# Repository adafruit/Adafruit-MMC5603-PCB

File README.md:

## Adafruit MMC5603 Triple-axis Magnetometer PCB

<a href="http://www.adafruit.com/products/5579"><br/>
Click here to purchase one from the Adafruit shop</a>

PCB files for the Adafruit MMC5603 Triple-axis Magnetometer. 

Format is EagleCAD schematic and board layout
* https://www.adafruit.com/product/5579

### Description

Sense the magnetic fields surrounding us with this handy triple-axis magnetometer (compass) module. Magnetometers can sense where the strongest magnetic force is coming from, generally used to detect magnetic north, but can also be used for measuring magnetic fields. This sensor tends to be paired with a 6-DoF (degree of freedom) accelerometer/gyroscope to create a 9-DoF inertial measurement unit that can detect its orientation in real-space thanks to Earth's stable magnetic field. It's a great match for the LSM6DSOX from ST!

We based this breakout on the MMC5603, a great general purpose magnetometer with a very wide range and bot I2C and SPI interfaces. This compact sensor uses I2C to communicate and it's very easy to use. Simply download our library and connect the SCL pin to your I2C clock pin, and SDA pin to your I2C data pin and upload our test program to read out magnetic field data. If you'd like, you can also use SPI to receive data (we just happen to prefer I2C here)

This sensor can sense ranges from ±30 Gauss (±3000uT or ±3mT) with no range-setting required and full 20 bit output up to 1000 Hz rate reading. The range makes it good for reading Earth's magnetic field (which maxes at about 0.6 Gauss) or some basic magnets. It isn't good for very strong rare earth magnets, for that check out the TLV293.

To make life easier so you can focus on your important work, we've taken the MMC5603 and put it onto a breakout PCB along with support circuitry to let you use this little wonder with 3.3V (Feather/Raspberry Pi) or 5V (Arduino/ Metro328) logic levels. Additionally, since it speaks I2C you can easily connect it up with two wires (plus power and ground!).  We've even included SparkFun qwiic compatible STEMMA QT connectors for the I2C bus so you don't even need to solder! Just wire up to your favorite micro and you can use our CircuitPython/Python or Arduino drivers to easily interface with the LIS2MDL and get magnetic measurements ASAP.

It's fully assembled and tested.  Comes with a bit of 0.1" standard header in case you want to use it with a breadboard or perfboard.  Four 2.5mm (0.1") mounting holes for easy attachment.

### License

Adafruit invests time and resources providing this open source design, please support Adafruit and open-source hardware by purchasing products from [Adafruit](https://www.adafruit.com)!

Designed by Limor Fried/Ladyada for Adafruit Industries.

Creative Commons Attribution/Share-Alike, all text above must be included in any redistribution. 
See license.txt for additional details.

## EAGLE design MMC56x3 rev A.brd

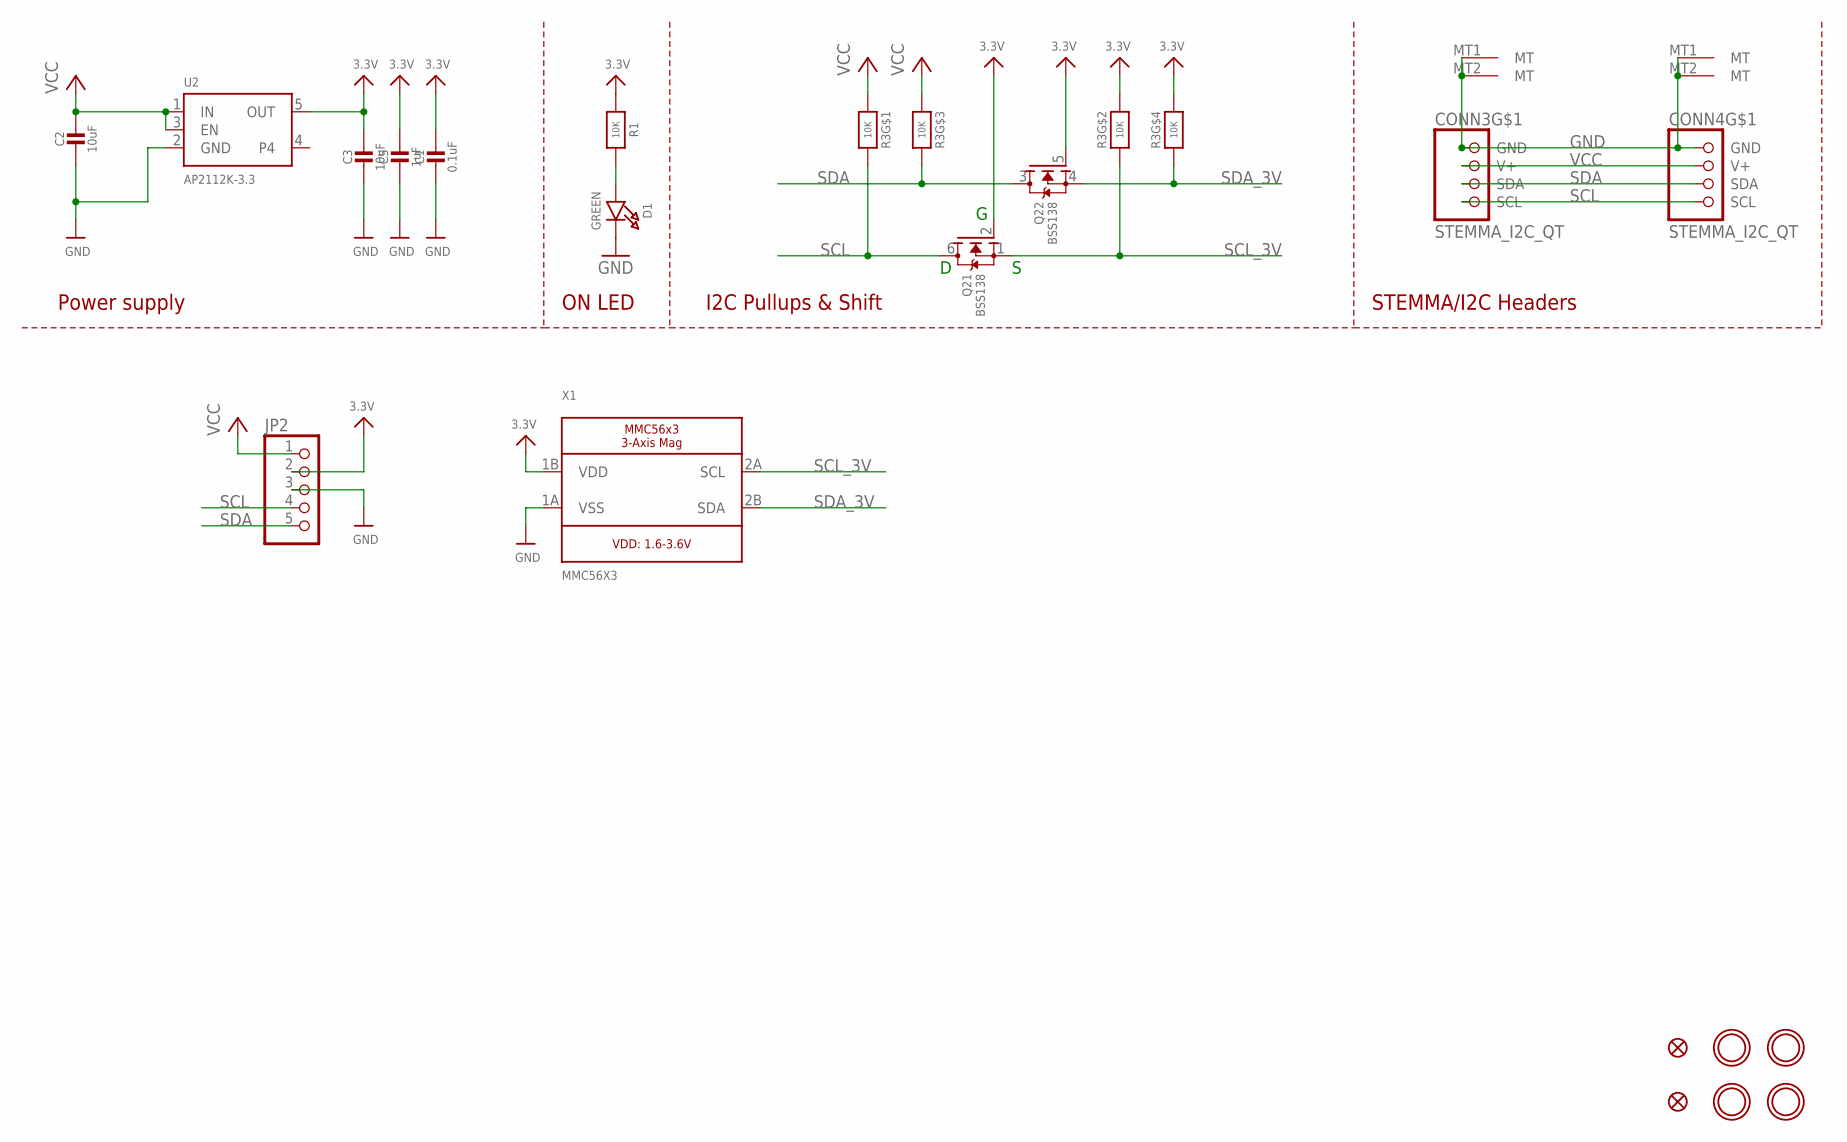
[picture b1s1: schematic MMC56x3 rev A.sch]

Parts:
C1: 0.1uF; 0603-NO
C2, C3: 10uF; 0805-NO
C5: 1uF; 0603-NO
CONN3, CONN4: STEMMA_I2C_QT; JST_SH4
D1: GREEN; CHIPLED_0603_NOOUTLINE
FID3, FID4: FIDUCIAL_1MM
JP2: HEADER-1X570MIL; 1X05_ROUND_70
Q2: BSS138; SOT363
R1: 10K; 0603-NO
R3: 10K; RESPACK_4X0603
U2: AP2112K-3.3; SOT23-5
U$1, U$2, U$4, U$17: MOUNTINGHOLE2.5; MOUNTINGHOLE_2.5_PLATED
X1: MMC56X3; WLP-4

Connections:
3.3V: C1.1, C3.1, C5.1, JP2.2, Q2.2 (G), Q2.5 (G), R1.1, R3.2 (1), R3.4 (1), U2.5 (OUT), X1.1B (VDD)
GND: C1.2, C2.2, C3.2, C5.2, CONN3.1 (GND), CONN3.MT1 (MT), CONN3.MT2 (MT), CONN4.1 (GND), CONN4.MT1 (MT), CONN4.MT2 (MT), D1.C, JP2.3, U2.2 (GND), X1.1A (VSS)
unnamed: D1.A, R1.2
SCL: CONN3.4 (SCL), CONN4.4 (SCL), JP2.4, Q2.6 (D), R3.8 (2)
SCL_3V: Q2.1 (S), R3.7 (2), X1.2A (SCL)
SDA: CONN3.3 (SDA), CONN4.3 (SDA), JP2.5, Q2.3 (D), R3.6 (2)
SDA_3V: Q2.4 (S), R3.5 (2), X1.2B (SDA)
VCC: C2.1, CONN3.2 (V+), CONN4.2 (V+), JP2.1, R3.1, R3.3 (1), U2.1 (IN), U2.3 (EN)

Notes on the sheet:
I2C Pullups & Shift
STEMMA/I2C Headers
ON LED
Power supply

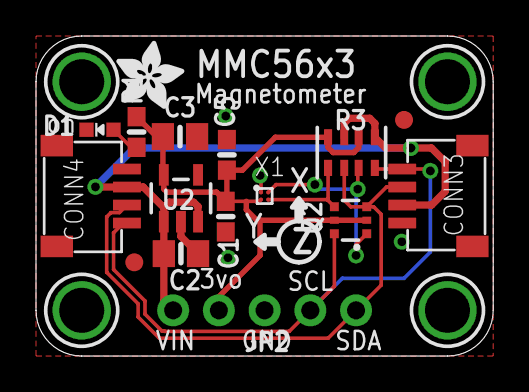
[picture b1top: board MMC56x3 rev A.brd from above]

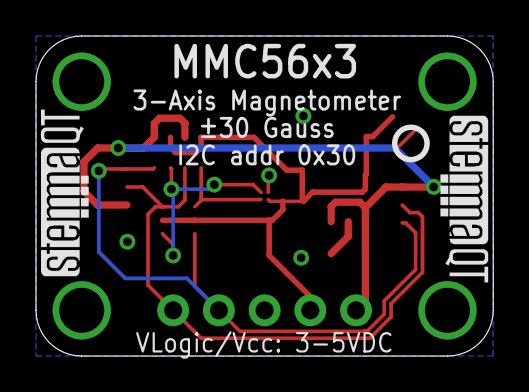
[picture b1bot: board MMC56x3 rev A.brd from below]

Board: 2 copper layers, 25.4 x 17.8 mm, 23 parts (3 on the bottom side), 8 nets.

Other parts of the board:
U$11: ADAFRUIT_3.5MM
U$25: PCBFEAT-REV-040
U$30, U$31: STEMMAQT

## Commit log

2022-08-04 Adding cookiecutter output

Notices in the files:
parts and their libraries:
microbuilder: This work is placed in the public domain, and may be freely used for commercial and non-commercial work with the following conditions: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
